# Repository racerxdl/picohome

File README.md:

# PicoHome (WIP)

Raspberry Pi Pico Home Automation using CAN Bus

**PLEASE READ LICENSE WARNING SECTION BEFORE USE**

This project is a improvement over my older home automation projects such as [espshift](https://github.com/racerxdl/esp32-shift). It all started when I wanted to make my own home automation project for learning and I didn't wanted to rely on Wireless Connections for my automation.

This project consists of few parts:

* [picohome-input](/pico-input/README.md) => Board with opto-coupled inputs which works from 12V to 24V switches.
* [picohome-relay](/pico-relay/README.md) => Board that fits on cheap chinese 16 relay board

The main idea is to be able to put everything inside a metal box and forget about it. So far I'm still iterating over designs (I'm running my own home automation for a few years already) and trying to make it less dependent of computers and such.

Work-in-progress = More details to come.

Universal firmware: https://github.com/racerxdl/piho

# LICENSE WARNING

Although all the code and schematics I did here is released under Apache / Creative Commons, the CAN2040 library is released under GPL. The creator of can2040 library doesn't seen to be willing to release it in another license (see https://github.com/KevinOConnor/can2040/issues/5 ) so basically since GPL is more restritive than the one I released, you should follow the GPL for this project.

So how that affects you? It will only affect you if you do distribute a binary version of the firmware. In this case GPL demands you to also release the source code. That's only likely to affect you if you're doing a commercial project and doesn't want to share the source code. Otherwise, you don't need to worry about it.

Although the can2040 library is GPL, everything else here will be as described in LICENSE. If anyone knows or want to do a replacement for can2040 library, let me know :D

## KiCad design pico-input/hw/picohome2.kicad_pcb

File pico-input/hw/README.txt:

Layout da placa rotacionado para que os cabos fiquem virados para baixo.
Corrigido o erro nas entradas PULL-UP paralelas, com adição de diodo Zener 15V para garantir que o sinal opto-acoplador só opere acima de 20V.
Retirado o pino MAGIC e colocado um borne duplo de 24V para ser utilizado como comum das entradas.

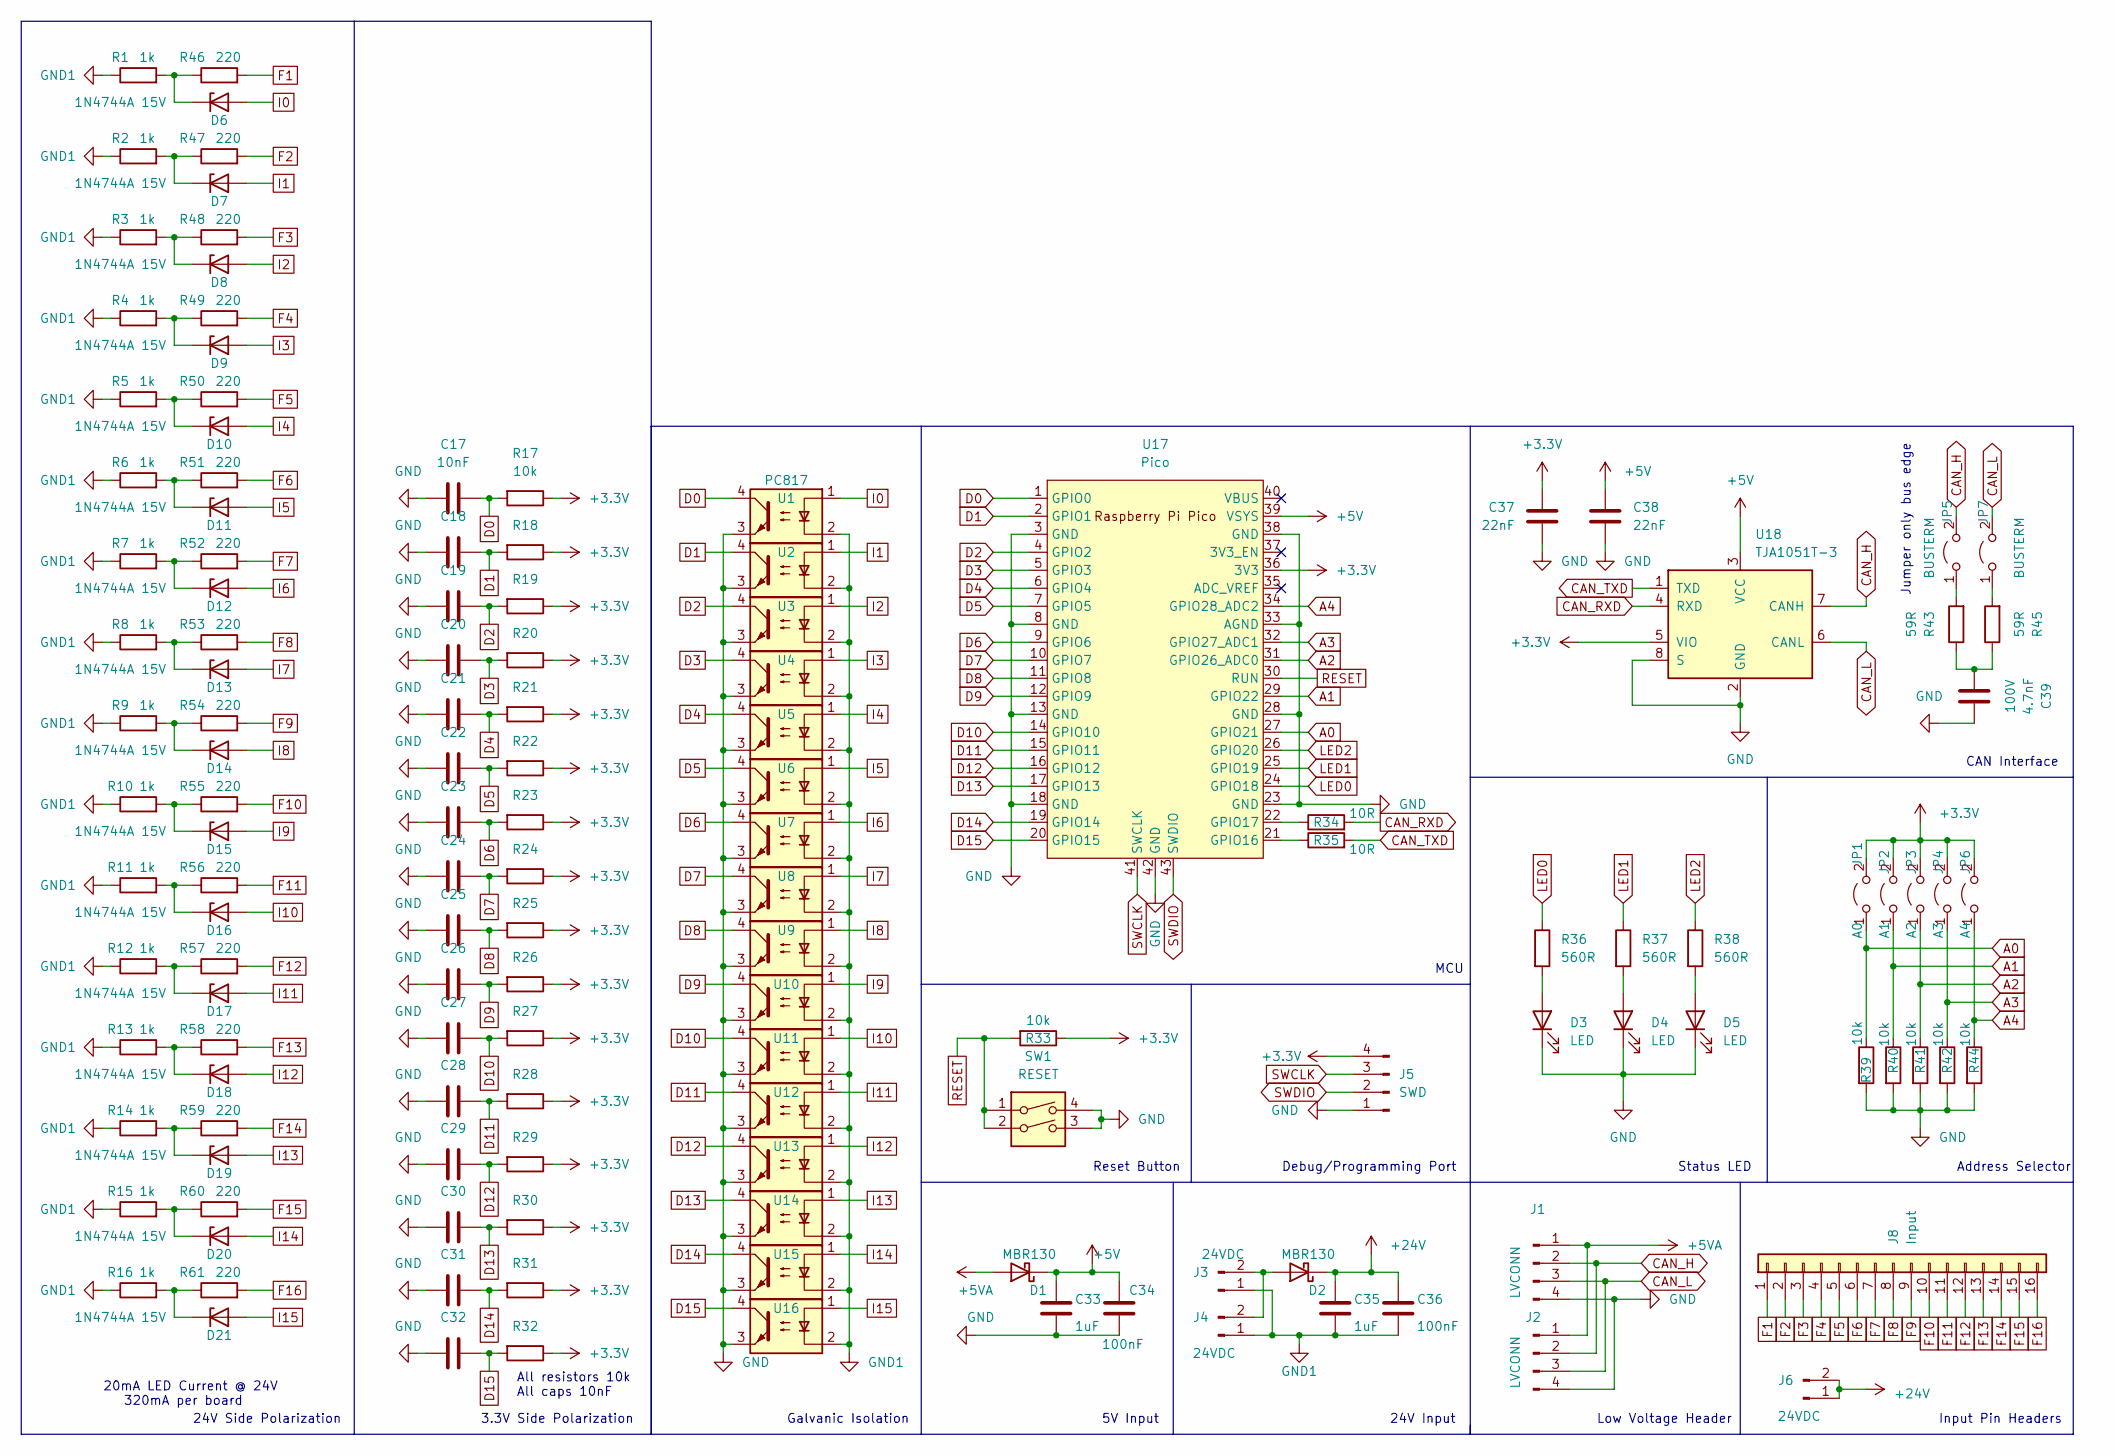
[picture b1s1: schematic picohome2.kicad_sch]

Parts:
C17, C18, C19, C20, C21, C22, C23, C24, C25, C26, C27, C28, C29, C30, C31, C32: 10nF; C_0805_2012Metric_Pad1.18x1.45mm_HandSolder
C33, C35: 1uF; C_0805_2012Metric_Pad1.18x1.45mm_HandSolder
C34, C36: 100nF; C_0805_2012Metric_Pad1.18x1.45mm_HandSolder
C37, C38: 22nF; C_0805_2012Metric_Pad1.18x1.45mm_HandSolder
C39: 4.7nF; C_0805_2012Metric_Pad1.18x1.45mm_HandSolder; Voltage 100V
D1, D2: MBR130; SOD-123_L2.7-W1.6-LS3.7-RD-1
D3, D4, D5: LED; LED_0805_2012Metric_Pad1.15x1.40mm_HandSolder
D6, D7, D8, D9, D10, D11, D12, D13, D14, D15, D16, D17, D18, D19, D20, D21: 1N4744A 15V; D_SOD-123
J1, J2: LVCONN; JST_XH_S4B-XH-A_1x04_P2.50mm_Horizontal
J3, J4, J6: 24VDC; Altech_AK300_1x02_P5.00mm_45-Degree
J5: SWD; JST_XH_B4B-XH-A_1x04_P2.50mm_Vertical
J8: Input; Altech_AK300_1x16_P5.00mm_45-Degree
JP1: A0; PinHeader_1x02_P2.54mm_Vertical
JP2: A1; PinHeader_1x02_P2.54mm_Vertical
JP3: A2; PinHeader_1x02_P2.54mm_Vertical
JP4: A3; PinHeader_1x02_P2.54mm_Vertical
JP5, JP7: BUSTERM; PinHeader_1x02_P2.54mm_Vertical
JP6: A4; PinHeader_1x02_P2.54mm_Vertical
R1, R2, R3, R4, R5, R6, R7, R8, R9, R10, R11, R12, R13, R14, R15, R16: 1k; R_0805_2012Metric_Pad1.20x1.40mm_HandSolder
R17, R18, R19, R20, R21, R22, R23, R24, R25, R26, R27, R28, R29, R30, R31, R32, R33, R39, R40, R41, R42, R44: 10k; R_0805_2012Metric_Pad1.20x1.40mm_HandSolder
R34, R35: 10R; R_0805_2012Metric_Pad1.20x1.40mm_HandSolder
R36, R37, R38: 560R; R_0805_2012Metric_Pad1.20x1.40mm_HandSolder
R43, R45: 59R; R_0805_2012Metric_Pad1.20x1.40mm_HandSolder
R46, R47, R48, R49, R50, R51, R52, R53, R54, R55, R56, R57, R58, R59, R60, R61: 220; R_0805_2012Metric_Pad1.20x1.40mm_HandSolder
SW1: RESET; SW-SMD_4P-L6.2-W6.2-P4.50-LS9.0
U1, U2, U3, U4, U5, U6, U7, U8, U9, U10, U11, U12, U13, U14, U15, U16: PC817; DIP-4_W7.62mm
U17: Pico; RPi_Pico_SMD_TH
U18: TJA1051T-3; SOIC-8_3.9x4.9mm_P1.27mm

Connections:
+3V3: C37.1, J5.4, JP1.2 (B), JP2.2 (B), JP3.2 (B), JP4.2 (B), JP6.2 (B), R17.1, R18.1, R19.1, R20.1, R21.1, R22.1, R23.1, R24.1, R25.1, R26.1, R27.1, R28.1, R29.1, R30.1, R31.1, R32.1, R33.1, U17.36 (3V3), U18.5 (VIO)
+5V: C33.1, C34.1, C38.1, D1.1 (K), U17.39 (VSYS), U18.3 (VCC)
+5VA: D1.2 (A), J1.1, J2.1
+24V: C35.1, C36.1, D2.1 (K), J6.1, J6.2
A0: JP1.1 (A), R39.1, U17.27 (GPIO21)
A1: JP2.1 (A), R40.1, U17.29 (GPIO22)
A2: JP3.1 (A), R41.1, U17.31 (GPIO26_ADC0)
A3: JP4.1 (A), R42.1, U17.32 (GPIO27_ADC1)
A4: JP6.1 (A), R44.1, U17.34 (GPIO28_ADC2)
CAN_H: J1.2, J2.2, JP5.2 (B), U18.7 (CANH)
CAN_L: J1.3, J2.3, JP7.2 (B), U18.6 (CANL)
CAN_RXD: R34.2, U18.4 (RXD)
CAN_TXD: R35.2, U18.1 (TXD)
D0: C17.2, R17.2, U1.4, U17.1 (GPIO0)
D1: C18.2, R18.2, U2.4, U17.2 (GPIO1)
D2: C19.2, R19.2, U3.4, U17.4 (GPIO2)
D3: C20.2, R20.2, U4.4, U17.5 (GPIO3)
D4: C21.2, R21.2, U5.4, U17.6 (GPIO4)
D5: C22.2, R22.2, U6.4, U17.7 (GPIO5)
D6: C23.2, R23.2, U7.4, U17.9 (GPIO6)
D7: C24.2, R24.2, U8.4, U17.10 (GPIO7)
D8: C25.2, R25.2, U9.4, U17.11 (GPIO8)
D9: C26.2, R26.2, U10.4, U17.12 (GPIO9)
D10: C27.2, R27.2, U11.4, U17.14 (GPIO10)
D11: C28.2, R28.2, U12.4, U17.15 (GPIO11)
D12: C29.2, R29.2, U13.4, U17.16 (GPIO12)
D13: C30.2, R30.2, U14.4, U17.17 (GPIO13)
D14: C31.2, R31.2, U15.4, U17.19 (GPIO14)
D15: C32.2, R32.2, U16.4, U17.20 (GPIO15)
F1: J8.1, R46.2
F2: J8.2, R47.2
F3: J8.3, R48.2
F4: J8.4, R49.2
F5: J8.5, R50.2
F6: J8.6, R51.2
F7: J8.7, R52.2
F8: J8.8, R53.2
F9: J8.9, R54.2
F10: J8.10, R55.2
F11: J8.11, R56.2
F12: J8.12, R57.2
F13: J8.13, R58.2
F14: J8.14, R59.2
F15: J8.15, R60.2
F16: J8.16, R61.2
GND: C17.1, C18.1, C19.1, C20.1, C21.1, C22.1, C23.1, C24.1, C25.1, C26.1, C27.1, C28.1, C29.1, C30.1, C31.1, C32.1, C33.2, C34.2, C37.2, C38.2, C39.2, D3.1 (K), D4.1 (K), D5.1 (K), J1.4, J2.4, J5.1, R39.2, R40.2, R41.2, R42.2, R44.2, SW1.3, SW1.4, U1.3, U2.3, U3.3, U4.3, U5.3, U6.3, U7.3, U8.3, U9.3, U10.3, U11.3, U12.3, U13.3, U14.3, U15.3, U16.3, U17.3 (GND), U17.8 (GND), U17.13 (GND), U17.18 (GND), U17.23 (GND), U17.28 (GND), U17.33 (AGND), U17.38 (GND), U17.42 (GND), U18.2 (GND), U18.8 (S)
GND1: C35.2, C36.2, J3.1, J4.1, R1.1, R2.1, R3.1, R4.1, R5.1, R6.1, R7.1, R8.1, R9.1, R10.1, R11.1, R12.1, R13.1, R14.1, R15.1, R16.1, U1.2, U2.2, U3.2, U4.2, U5.2, U6.2, U7.2, U8.2, U9.2, U10.2, U11.2, U12.2, U13.2, U14.2, U15.2, U16.2
I0: D6.2 (A), U1.1
I1: D7.2 (A), U2.1
I2: D8.2 (A), U3.1
I3: D9.2 (A), U4.1
I4: D10.2 (A), U5.1
I5: D11.2 (A), U6.1
I6: D12.2 (A), U7.1
I7: D13.2 (A), U8.1
I8: D14.2 (A), U9.1
I9: D15.2 (A), U10.1
I10: D16.2 (A), U11.1
I11: D17.2 (A), U12.1
I12: D18.2 (A), U13.1
I13: D19.2 (A), U14.1
I14: D20.2 (A), U15.1
I15: D21.2 (A), U16.1
LED0: R36.1, U17.24 (GPIO18)
LED1: R37.1, U17.25 (GPIO19)
LED2: R38.1, U17.26 (GPIO20)
unnamed: C39.1, R43.1, R45.1
unnamed: D2.2 (A), J3.2, J4.2
unnamed: D3.2 (A), R36.2
unnamed: D4.2 (A), R37.2
unnamed: D5.2 (A), R38.2
unnamed: D6.1 (K), R1.2, R46.1
unnamed: D7.1 (K), R2.2, R47.1
unnamed: D8.1 (K), R3.2, R48.1
unnamed: D9.1 (K), R4.2, R49.1
unnamed: D10.1 (K), R5.2, R50.1
unnamed: D11.1 (K), R6.2, R51.1
unnamed: D12.1 (K), R7.2, R52.1
unnamed: D13.1 (K), R8.2, R53.1
unnamed: D14.1 (K), R9.2, R54.1
unnamed: D15.1 (K), R10.2, R55.1
unnamed: D16.1 (K), R11.2, R56.1
unnamed: D17.1 (K), R12.2, R57.1
unnamed: D18.1 (K), R13.2, R58.1
unnamed: D19.1 (K), R14.2, R59.1
unnamed: D20.1 (K), R15.2, R60.1
unnamed: D21.1 (K), R16.2, R61.1
unnamed: JP5.1 (A), R43.2
unnamed: JP7.1 (A), R45.2
unnamed: R35.1, U17.21 (GPIO16)
unnamed: R34.1, U17.22 (GPIO17)
RESET: R33.2, SW1.1, SW1.2, U17.30 (RUN)
SWCLK: J5.3, U17.41 (SWCLK)
SWDIO: J5.2, U17.43 (SWDIO)

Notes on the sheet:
20mA LED Current @ 24V 320mA per board
Galvanic Isolation
5V Input
Low Voltage Header
Jumper only bus edge
Debug/Programming Port
Input Pin Headers
CAN Interface
3.3V Side Polarization
Reset Button
MCU
Address Selector
All resistors 10k All caps 10nF
24V Input
24V Side Polarization
Status LED

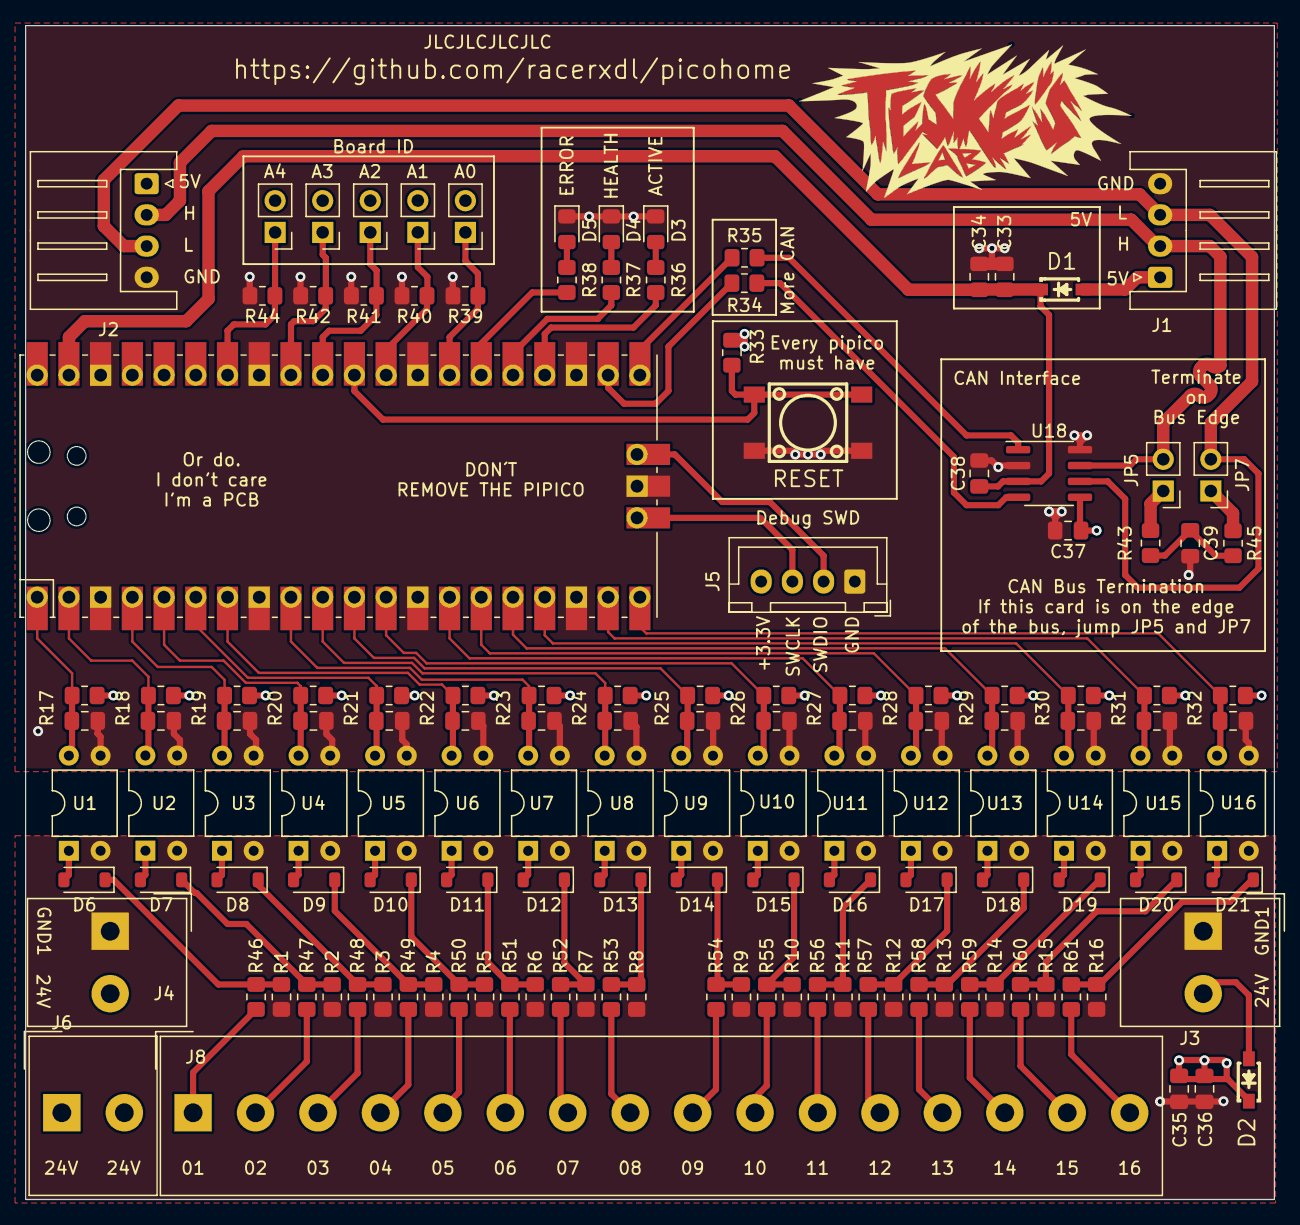
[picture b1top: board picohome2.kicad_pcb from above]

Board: 4 copper layers, 100.0 x 94.0 mm, 138 parts (0 on the bottom side), 94 nets.

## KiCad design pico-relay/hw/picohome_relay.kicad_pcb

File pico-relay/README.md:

# pico-relay

This board is part of picohome project. It features:

* CAN Bus - Fully controlled through CAN
* 5 bit address - Up to 32 boards in the same CAN bus
* 16 open-collector 200mA outputs that can switch relays up to 24V
* Design to fit over a chinese 16 relay board

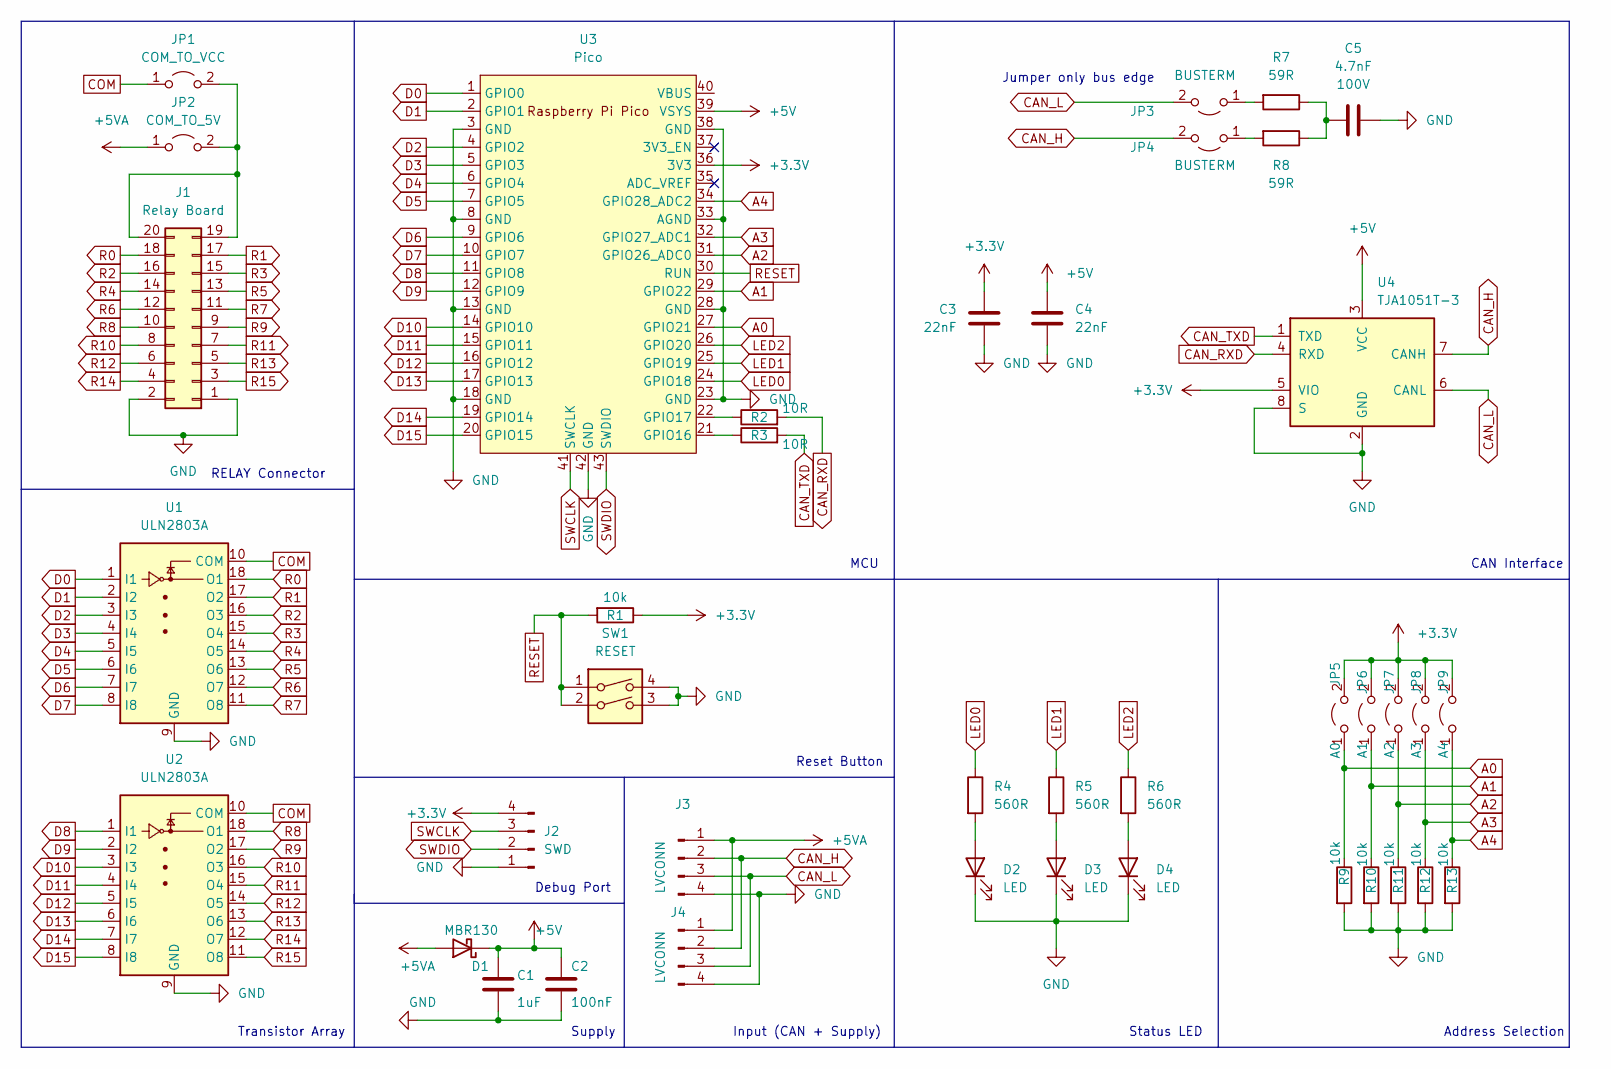
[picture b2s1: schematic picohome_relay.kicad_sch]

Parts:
C1: 1uF; C_0805_2012Metric_Pad1.18x1.45mm_HandSolder
C2: 100nF; C_0805_2012Metric_Pad1.18x1.45mm_HandSolder
C3, C4: 22nF; C_0805_2012Metric_Pad1.18x1.45mm_HandSolder
C5: 4.7nF; C_0805_2012Metric_Pad1.18x1.45mm_HandSolder; Voltage 100V
D1: MBR130; SOD-123_L2.7-W1.6-LS3.7-RD-1
D2, D3, D4: LED; LED_0805_2012Metric_Pad1.15x1.40mm_HandSolder
J1: Relay Board; PinSocket_2x10_P2.54mm_Vertical
J2: SWD; JST_XH_B4B-XH-A_1x04_P2.50mm_Vertical
J3, J4: LVCONN; JST_XH_S4B-XH-A_1x04_P2.50mm_Horizontal
JP1: COM_TO_VCC; PinHeader_1x02_P2.54mm_Vertical
JP2: COM_TO_5V; PinHeader_1x02_P2.54mm_Vertical
JP3, JP4: BUSTERM; PinHeader_1x02_P2.54mm_Vertical
JP5: A0; PinHeader_1x02_P2.54mm_Vertical
JP6: A1; PinHeader_1x02_P2.54mm_Vertical
JP7: A2; PinHeader_1x02_P2.54mm_Vertical
JP8: A3; PinHeader_1x02_P2.54mm_Vertical
JP9: A4; PinHeader_1x02_P2.54mm_Vertical
R1, R9, R10, R11, R12, R13: 10k; R_0805_2012Metric_Pad1.20x1.40mm_HandSolder
R2, R3: 10R; R_0805_2012Metric_Pad1.20x1.40mm_HandSolder
R4, R5, R6: 560R; R_0805_2012Metric_Pad1.20x1.40mm_HandSolder
R7, R8: 59R; R_0805_2012Metric_Pad1.20x1.40mm_HandSolder
SW1: RESET; SW-SMD_4P-L6.2-W6.2-P4.50-LS9.0
U1, U2: ULN2803A; SOIC-18W_7.5x11.6mm_P1.27mm
U3: Pico; RPi_Pico_SMD_TH
U4: TJA1051T-3; SOIC-8_3.9x4.9mm_P1.27mm

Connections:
+3V3: C3.1, J2.4, JP5.2 (B), JP6.2 (B), JP7.2 (B), JP8.2 (B), JP9.2 (B), R1.1, U3.36 (3V3), U4.5 (VIO)
+5V: C1.1, C2.1, C4.1, D1.1 (K), U3.39 (VSYS), U4.3 (VCC)
+5VA: D1.2 (A), J3.1, J4.1, JP2.1 (A)
A0: JP5.1 (A), R9.1, U3.27 (GPIO21)
A1: JP6.1 (A), R10.1, U3.29 (GPIO22)
A2: JP7.1 (A), R11.1, U3.31 (GPIO26_ADC0)
A3: JP8.1 (A), R12.1, U3.32 (GPIO27_ADC1)
A4: JP9.1 (A), R13.1, U3.34 (GPIO28_ADC2)
CAN_H: J3.2, J4.2, JP4.2 (B), U4.7 (CANH)
CAN_L: J3.3, J4.3, JP3.2 (B), U4.6 (CANL)
CAN_RXD: R2.2, U4.4 (RXD)
CAN_TXD: R3.2, U4.1 (TXD)
COM: JP1.1 (A), U1.10 (COM), U2.10 (COM)
D0: U1.1 (I1), U3.1 (GPIO0)
D1: U1.2 (I2), U3.2 (GPIO1)
D2: U1.3 (I3), U3.4 (GPIO2)
D3: U1.4 (I4), U3.5 (GPIO3)
D4: U1.5 (I5), U3.6 (GPIO4)
D5: U1.6 (I6), U3.7 (GPIO5)
D6: U1.7 (I7), U3.9 (GPIO6)
D7: U1.8 (I8), U3.10 (GPIO7)
D8: U2.1 (I1), U3.11 (GPIO8)
D9: U2.2 (I2), U3.12 (GPIO9)
D10: U2.3 (I3), U3.14 (GPIO10)
D11: U2.4 (I4), U3.15 (GPIO11)
D12: U2.5 (I5), U3.16 (GPIO12)
D13: U2.6 (I6), U3.17 (GPIO13)
D14: U2.7 (I7), U3.19 (GPIO14)
D15: U2.8 (I8), U3.20 (GPIO15)
GND: C1.2, C2.2, C3.2, C4.2, C5.2, D2.1 (K), D3.1 (K), D4.1 (K), J1.1, J1.2, J2.1, J3.4, J4.4, R9.2, R10.2, R11.2, R12.2, R13.2, SW1.3, SW1.4, U1.9 (GND), U2.9 (GND), U3.3 (GND), U3.8 (GND), U3.13 (GND), U3.18 (GND), U3.23 (GND), U3.28 (GND), U3.33 (AGND), U3.38 (GND), U3.42 (GND), U4.2 (GND), U4.8 (S)
LED0: R4.1, U3.24 (GPIO18)
LED1: R5.1, U3.25 (GPIO19)
LED2: R6.1, U3.26 (GPIO20)
unnamed: C5.1, R7.1, R8.1
unnamed: D2.2 (A), R4.2
unnamed: D3.2 (A), R5.2
unnamed: D4.2 (A), R6.2
unnamed: J1.19, J1.20, JP1.2 (B), JP2.2 (B)
unnamed: JP3.1 (A), R7.2
unnamed: JP4.1 (A), R8.2
unnamed: R2.1, U3.22 (GPIO17)
unnamed: R3.1, U3.21 (GPIO16)
R0: J1.18, U1.18 (O1)
R1: J1.17, U1.17 (O2)
R2: J1.16, U1.16 (O3)
R3: J1.15, U1.15 (O4)
R4: J1.14, U1.14 (O5)
R5: J1.13, U1.13 (O6)
R6: J1.12, U1.12 (O7)
R7: J1.11, U1.11 (O8)
R8: J1.10, U2.18 (O1)
R9: J1.9, U2.17 (O2)
R10: J1.8, U2.16 (O3)
R11: J1.7, U2.15 (O4)
R12: J1.6, U2.14 (O5)
R13: J1.5, U2.13 (O6)
R14: J1.4, U2.12 (O7)
R15: J1.3, U2.11 (O8)
RESET: R1.2, SW1.1, SW1.2, U3.30 (RUN)
SWCLK: J2.3, U3.41 (SWCLK)
SWDIO: J2.2, U3.43 (SWDIO)

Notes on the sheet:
CAN Interface
Address Selection
Transistor Array
Debug Port
MCU
RELAY Connector
Jumper only bus edge
Status LED
Reset Button
Supply
Input (CAN + Supply)

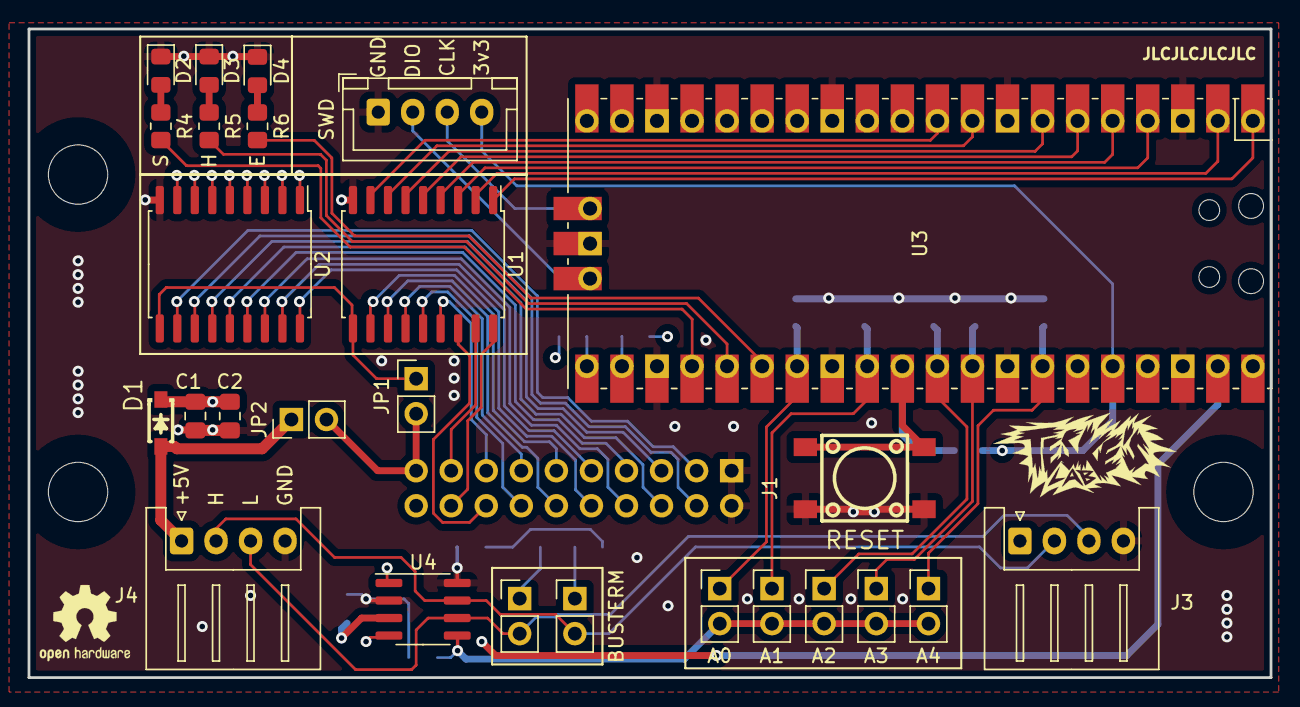
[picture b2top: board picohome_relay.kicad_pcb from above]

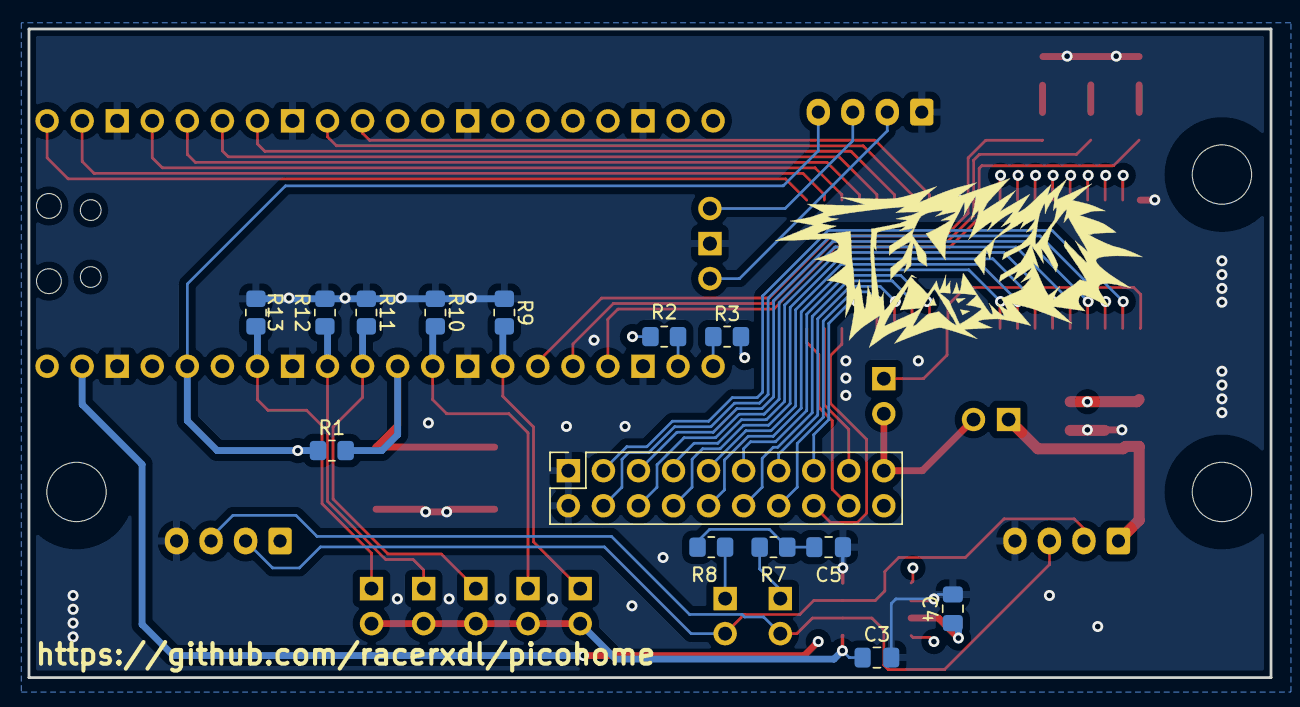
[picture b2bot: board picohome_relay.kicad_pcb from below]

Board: 4 copper layers, 90.0 x 47.0 mm, 40 parts (14 on the bottom side), 61 nets.

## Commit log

2022-09-05 Add pico-input alfa
2022-09-05 Add FUNDING
2022-09-05 Add pico-input README
2022-09-11 Add picohome relay board
2022-10-16 Updated input control to real board.
2023-01-23 Removed firmware (now in another repository)
2023-01-23 Update 24V Pull-up resistors to 10k (2k7 dissipates too much heat)
2023-04-22 Add files via upload
    Rotacionada a orientação da placa para que os cabos fiquem virados para baixo.
    Corrigido as entradas de 24VDC e adicionado diodo Zener 15V para garantir que o sinal opto-acoplador só opere acima de 20V.
    Retirado o pino MAGIC e colocado um borne duplo de 24V para ser utilizado como comum das entradas.
